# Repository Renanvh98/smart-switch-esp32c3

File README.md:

# Smart Switch PCB — ESP32-C3

Placa de circuito impresso para interruptor inteligente de parede, desenvolvida com o ESP32-C3 para automação residencial via Wi-Fi.

## Visualização da PCB

### Vista 3D principal

### Vista 3D — detalhe 1

### Vista 3D — detalhe 2

## Especificações técnicas

- **Microcontrolador:** ESP32-C3-WROOM-02
- **Alimentação:** módulo AC-DC HS-40012, entrada 127/220 V AC e saída de 12 V DC
- **Regulação lógica:** AZ1117CH-3.3, saída de 3,3 V
- **Relé:** SRD-12VDC-SL-C
- **Acionamento:** MOSFET canal N
- **Programação:** interface UART de 4 pinos
- **Aplicação:** automação residencial e controle de cargas elétricas

## Arquivos do projeto

| Arquivo | Descrição |
|---|---|
| `fonte_rele_esp-c3.kicad_pro` | Projeto KiCad |
| `fonte_rele_esp-c3.kicad_sch` | Esquemático elétrico |
| `fonte_rele_esp-c3.kicad_pcb` | Layout da placa |
| `images/` | Renderizações 3D da PCB |

## Observações de hardware

O contato COM do relé é disponibilizado separadamente do terminal de entrada de fase da placa. A ligação externa deve ser feita somente após verificar o esquema elétrico e as condições de segurança da instalação.

**Atenção:** a placa envolve tensão de rede elétrica. A separação entre alta e baixa tensão, o dimensionamento das trilhas, a proteção por fusível e as distâncias de isolamento devem ser validados antes da fabricação e utilização.

## English

Smart wall-switch PCB based on the ESP32-C3 for Wi-Fi home automation. The design integrates AC-DC power conversion, 3.3 V logic regulation, relay control and UART programming.

The repository contains the KiCad project, electrical schematic, PCB layout and 3D board renders.

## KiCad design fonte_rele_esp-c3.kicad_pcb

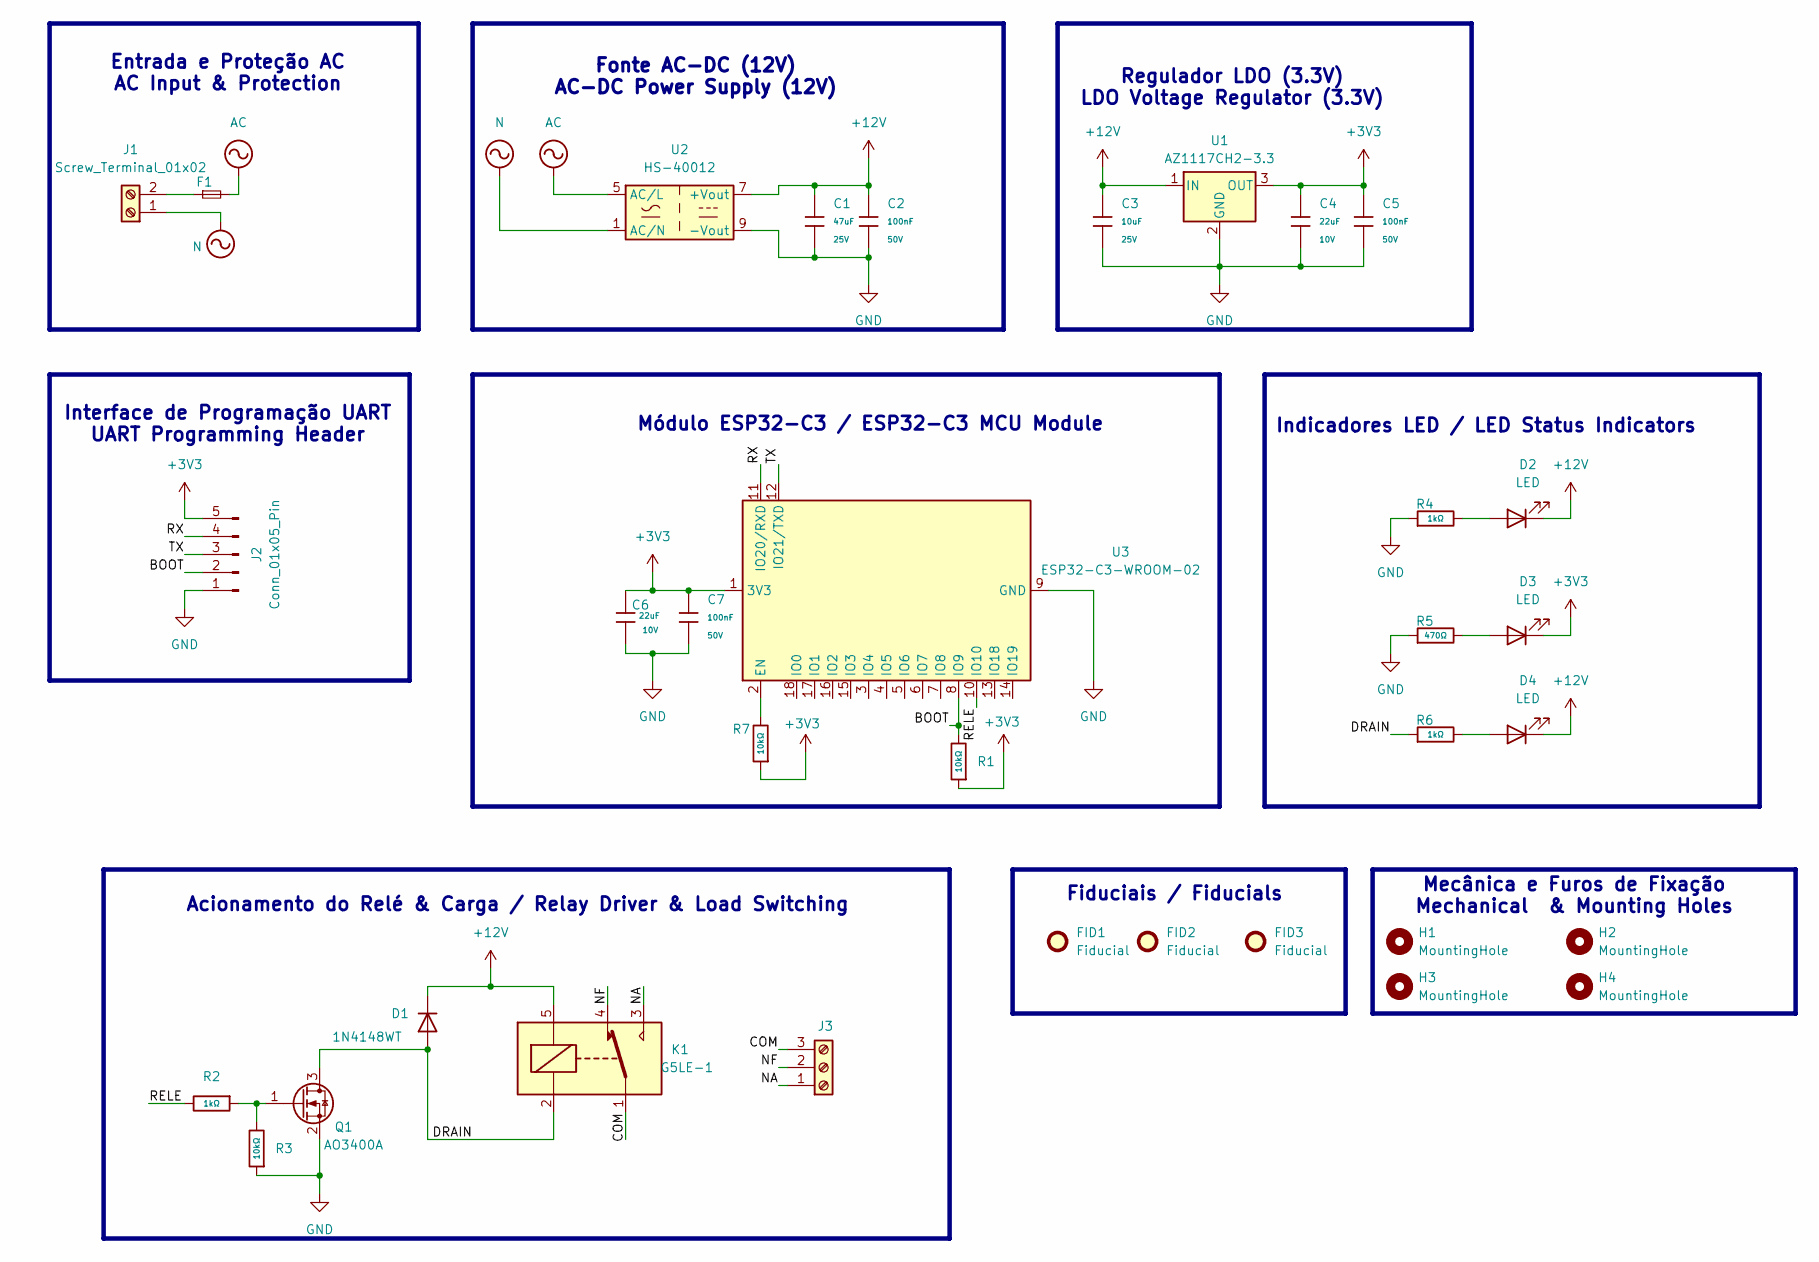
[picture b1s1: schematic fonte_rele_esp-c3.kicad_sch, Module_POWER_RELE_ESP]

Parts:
C1: 47uF; C_1206; Voltage Rated 25V; Tolerance ±20%; Part CL31A476MPHNNNE; LCSC C96123
C2, C5, C7: 100nF; C_0603; Voltage Rated 50V; Tolerance ±10%; Part CC0603KRX7R9BB104; LCSC C14663
C3: 10uF; C_0805; Voltage Rated 25V; Tolerance ±10%; Part CL21A106KAYNNNE; LCSC C15850
C4, C6: 22uF; C_1206; Voltage Rated 10V; Tolerance ±10%; Part CL31A226KPHNNNE; LCSC C5672
D1: 1N4148WT; D_SOD-523
D2, D3, D4: LED; LED_0805_2012Metric
F1: Fuse_Small; Fuseholder_Littelfuse_Nano2_157x
FID1, FID2, FID3: Fiducial; Fiducial_0.5mm_Mask1mm
H1, H2, H3, H4: MountingHole; MountingHole_2.2mm_M2
J1: Screw_Terminal_01x02; TerminalBlock_MetzConnect_Type094_RT03502HBLU_1x02_P5.00mm_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
J2: Conn_01x05_Pin; PinHeader_1x05_P2.54mm_Vertical
J3: Screw_Terminal_01x03; TerminalBlock_MetzConnect_Type094_RT03503HBLU_1x03_P5.00mm_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
K1: G5LE-1; Relay_SPDT_Omron-G5LE-1
Q1: AO3400A; SOT-23
R1, R3: 10kΩ; R_0603; Overload Voltage (Max) 75V; Tolerance ±1%; Part 0603WAF1002T5E; LCSC C25804
R2: 1kΩ; R_0603; Overload Voltage (Max) 75V; Tolerance ±1%; Part 0603WAF1001T5E; LCSC C21190
R4, R6: 1kΩ; R_0805; Overload Voltage (Max) 150V; Tolerance ±1%; Part 0805W8F1001T5E; LCSC C17513
R5: 470Ω; R_0805; Overload Voltage (Max) 150V; Tolerance ±1%; Part 0805W8F4700T5E; LCSC C17710
R7: 10kΩ; R_0603_1608Metric; Overload Voltage (Max) 75V; Tolerance ±1%; Part 0603WAF1002T5E; LCSC C25804
U1: AZ1117CH2-3.3; SOT-223-3_TabPin2
U2: HS-40012; Converter_ACDC_Hahn_HS-400xx_THT
U3: ESP32-C3-WROOM-02

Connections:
+3V3: C4.1, C5.1, C6.1, C7.1, D3.1 (K), J2.5, R1.1, R7.1, U1.3 (OUT), U3.1 (3V3)
+12V: C1.1, C2.1, C3.1, D1.1 (K), D2.1 (K), D4.1 (K), K1.5, U1.1 (IN), U2.7 (+Vout)
/BOOT: J2.2, R1.2, U3.8 (IO9)
/COM: J3.3, K1.1
/DRAIN: D1.2 (A), K1.2, Q1.3 (D), R6.1
/NA: J3.1, K1.3
/NF: J3.2, K1.4
/RELE: R2.2, U3.10 (IO10)
/RX: J2.4, U3.11 (IO20/RXD)
/TX: J2.3, U3.12 (IO21/TXD)
AC: F1.2, U2.5 (AC/L)
GND: C1.2, C2.2, C3.2, C4.2, C5.2, C6.2, C7.2, J2.1, Q1.2 (S), R3.1, R4.1, R5.1, U1.2 (GND), U2.9 (-Vout), U3.9 (GND), U3.19 (GND)
N: J1.1, U2.1 (AC/N)
unnamed: D2.2 (A), R4.2
unnamed: D3.2 (A), R5.2
unnamed: D4.2 (A), R6.2
unnamed: F1.1, J1.2
unnamed: Q1.1 (G), R2.1, R3.2
unnamed: R7.2, U3.2 (EN)

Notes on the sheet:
Fiduciais / Fiducials
Mecânica e Furos de Fixação Mechanical & Mounting Holes
Indicadores LED / LED Status Indicators
Acionamento do Relé & Carga / Relay Driver & Load Switching
Regulador LDO (3.3V) LDO Voltage Regulator (3.3V)
Fonte AC-DC (12V) AC-DC Power Supply (12V)
Interface de Programação UART UART Programming Header
Módulo ESP32-C3 / ESP32-C3 MCU Module
Entrada e Proteção AC AC Input & Protection

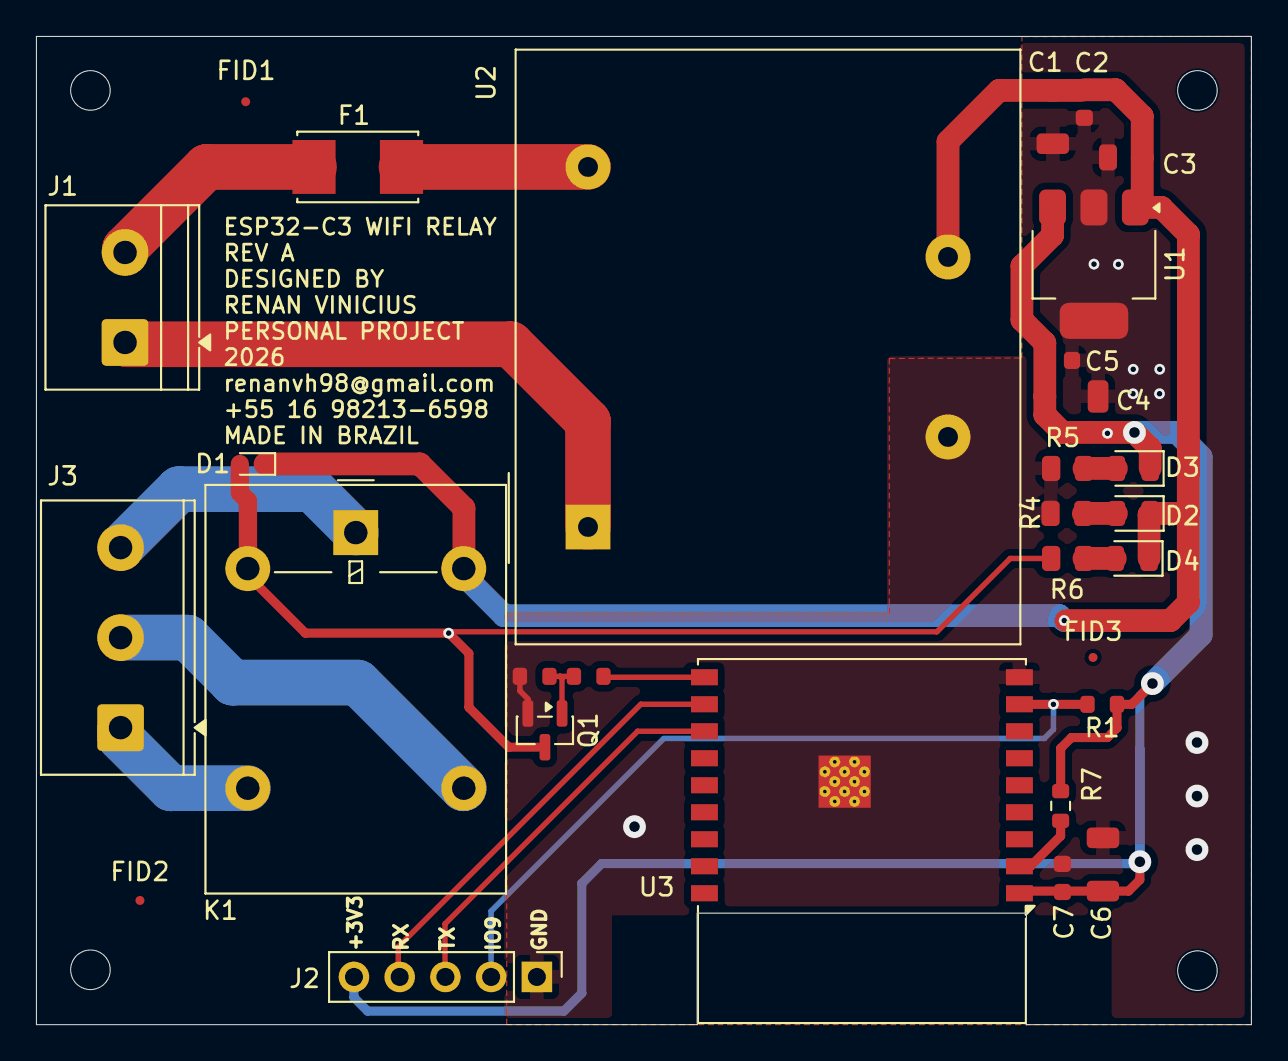
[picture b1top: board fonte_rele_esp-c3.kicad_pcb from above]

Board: 2 copper layers, 67.5 x 54.9 mm, 34 parts (0 on the bottom side), 19 nets.
